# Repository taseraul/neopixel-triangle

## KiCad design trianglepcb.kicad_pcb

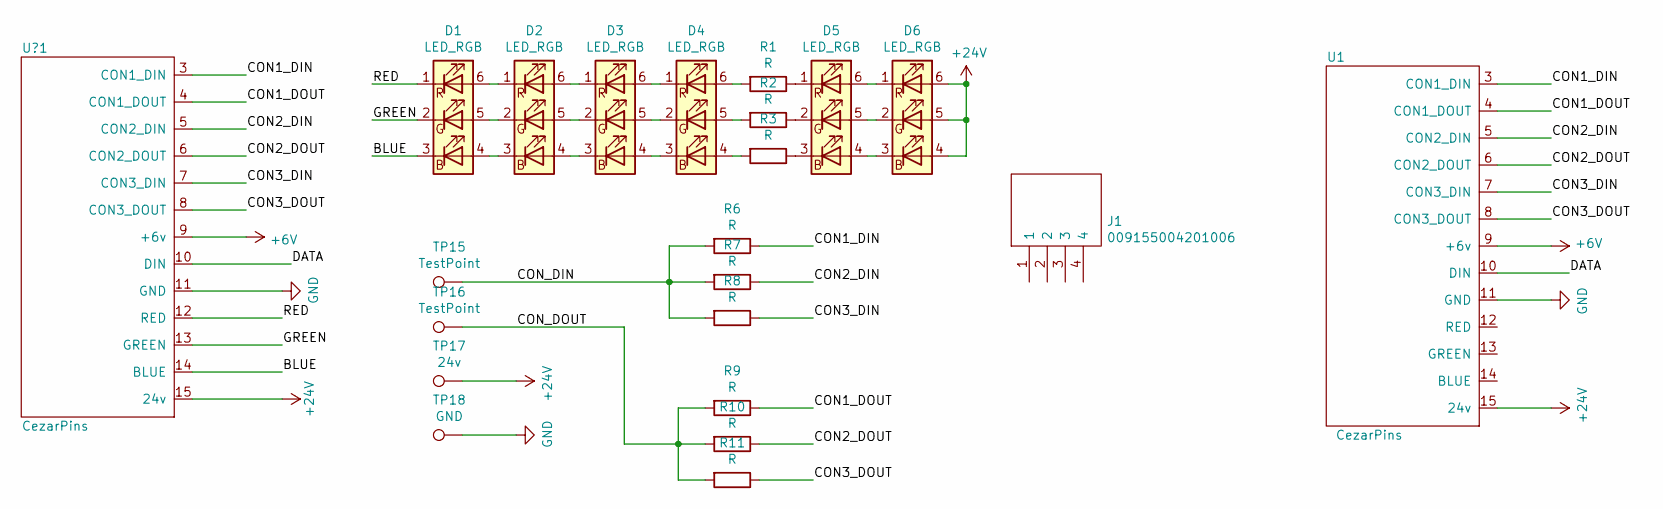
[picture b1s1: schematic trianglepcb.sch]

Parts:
D1, D2, D3, D4, D5, D6: LED_RGB; LED_RGB_5050-6
J1: 009155004201006; Mouser Part Number 581-009155004201006
R1, R2, R3, R6, R7, R8, R9, R10, R11: R; R_0402_1005Metric_Pad0.72x0.64mm_HandSolder
TP15, TP16: TestPoint; TestPoint_Pad_1.0x1.0mm
TP17: 24v; TestPoint_Pad_1.0x1.0mm
TP18: GND; TestPoint_Pad_1.0x1.0mm
U1: CezarPins
U?1: CezarPins

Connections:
+6V: U1.9 (+6v), U?1.9 (+6v)
+24V: D6.4 (BA), D6.5 (GA), D6.6 (RA), TP17.1, U1.15 (24v), U?1.15 (24v)
/BLUE: D1.3 (BK), U?1.14 (BLUE)
/CON1_DIN: R6.1, U1.3 (CON1_DIN), U?1.3 (CON1_DIN)
/CON1_DOUT: R9.1, U1.4 (CON1_DOUT), U?1.4 (CON1_DOUT)
/CON2_DIN: R7.1, U1.5 (CON2_DIN), U?1.5 (CON2_DIN)
/CON2_DOUT: R10.1, U1.6 (CON2_DOUT), U?1.6 (CON2_DOUT)
/CON3_DIN: R8.1, U1.7 (CON3_DIN), U?1.7 (CON3_DIN)
/CON3_DOUT: R11.1, U1.8 (CON3_DOUT), U?1.8 (CON3_DOUT)
/CON_DIN: R6.2, R7.2, R8.2, TP15.1
/CON_DOUT: R9.2, R10.2, R11.2, TP16.1
/DATA: U1.10 (DIN), U?1.10 (DIN)
/GREEN: D1.2 (GK), U?1.13 (GREEN)
/RED: D1.1 (RK), U?1.12 (RED)
GND: TP18.1, U1.11 (GND), U?1.11 (GND)
unnamed: D1.4 (BA), D2.3 (BK)
unnamed: D1.5 (GA), D2.2 (GK)
unnamed: D1.6 (RA), D2.1 (RK)
unnamed: D2.4 (BA), D3.3 (BK)
unnamed: D2.5 (GA), D3.2 (GK)
unnamed: D2.6 (RA), D3.1 (RK)
unnamed: D3.4 (BA), D4.3 (BK)
unnamed: D3.5 (GA), D4.2 (GK)
unnamed: D3.6 (RA), D4.1 (RK)
unnamed: D4.4 (BA), R3.2
unnamed: D4.5 (GA), R2.2
unnamed: D4.6 (RA), R1.2
unnamed: D5.1 (RK), R1.1
unnamed: D5.2 (GK), R2.1
unnamed: D5.3 (BK), R3.1
unnamed: D5.4 (BA), D6.3 (BK)
unnamed: D5.5 (GA), D6.2 (GK)
unnamed: D5.6 (RA), D6.1 (RK)

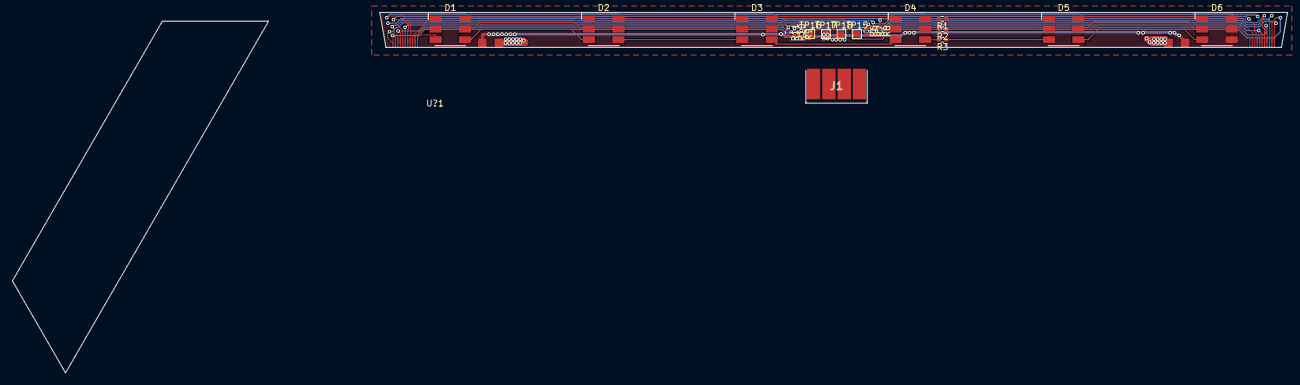
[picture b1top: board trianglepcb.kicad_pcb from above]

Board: 4 copper layers, 207.9 x 58.8 mm, 22 parts (0 on the bottom side), 33 nets.
